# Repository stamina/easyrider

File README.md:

EasyRider
=========

EasyRider is a motorcycle telemetrics project, developed specifically for my Honda C90 classic bike.

The software is written in C for the Atmel AVR ATmega1284p main microcontroller.

The PCB was created with CadSoft Eagle 6.x, you'll find the schematic and board layout (including all components) in the /eagle directory.
The file /doc/info.txt also contains the [BOM] and some project notes. (Partly in Dutch)

_UPDATE:_ EasyRider REV B (github repo: easyriderb) is a completely new, smaller and more advanced board (mostly SMD parts) which also contains a GPS and WiFi module
for easy tracking and communicating with a mobile phone app.

Functionality
-------------

EasyRider basically does the following things:

- Controls the lighting system: indicators, rear light, brake light, etc.
- Controls the claxon
- Contains a simple alarm system, based on an accelerometer
- Reads the motorcycle battery and gives a visual indication of the current voltage
- Contains a little buzzer for some funny startup sounds
- Contains a custom serial UART shell for communication with a terminal program or another microcontroller

Software
--------

The sofware is built around a simple *State Machine* pattern: when the driver is braking or toggling a switch, the software
is sending an event, which is handled by the correct event handler based on the current state (a bitmask of multiple substates).

The buzzer music was created with the **MIDICSV** MIDI to CSV conversion tool. The midi2byte.rb Ruby script converts the
plaintext CSV to a C header file containing an array of music notes.

The custom UART shell code is capable of registering commands and command handlers. E.g. typing "help" or "show state" in TeraTerm, Minicom, Putty
or any other serial terminal program. (configuration: 19200 baud/8N1)

*[BOM]: Bill Of Materials

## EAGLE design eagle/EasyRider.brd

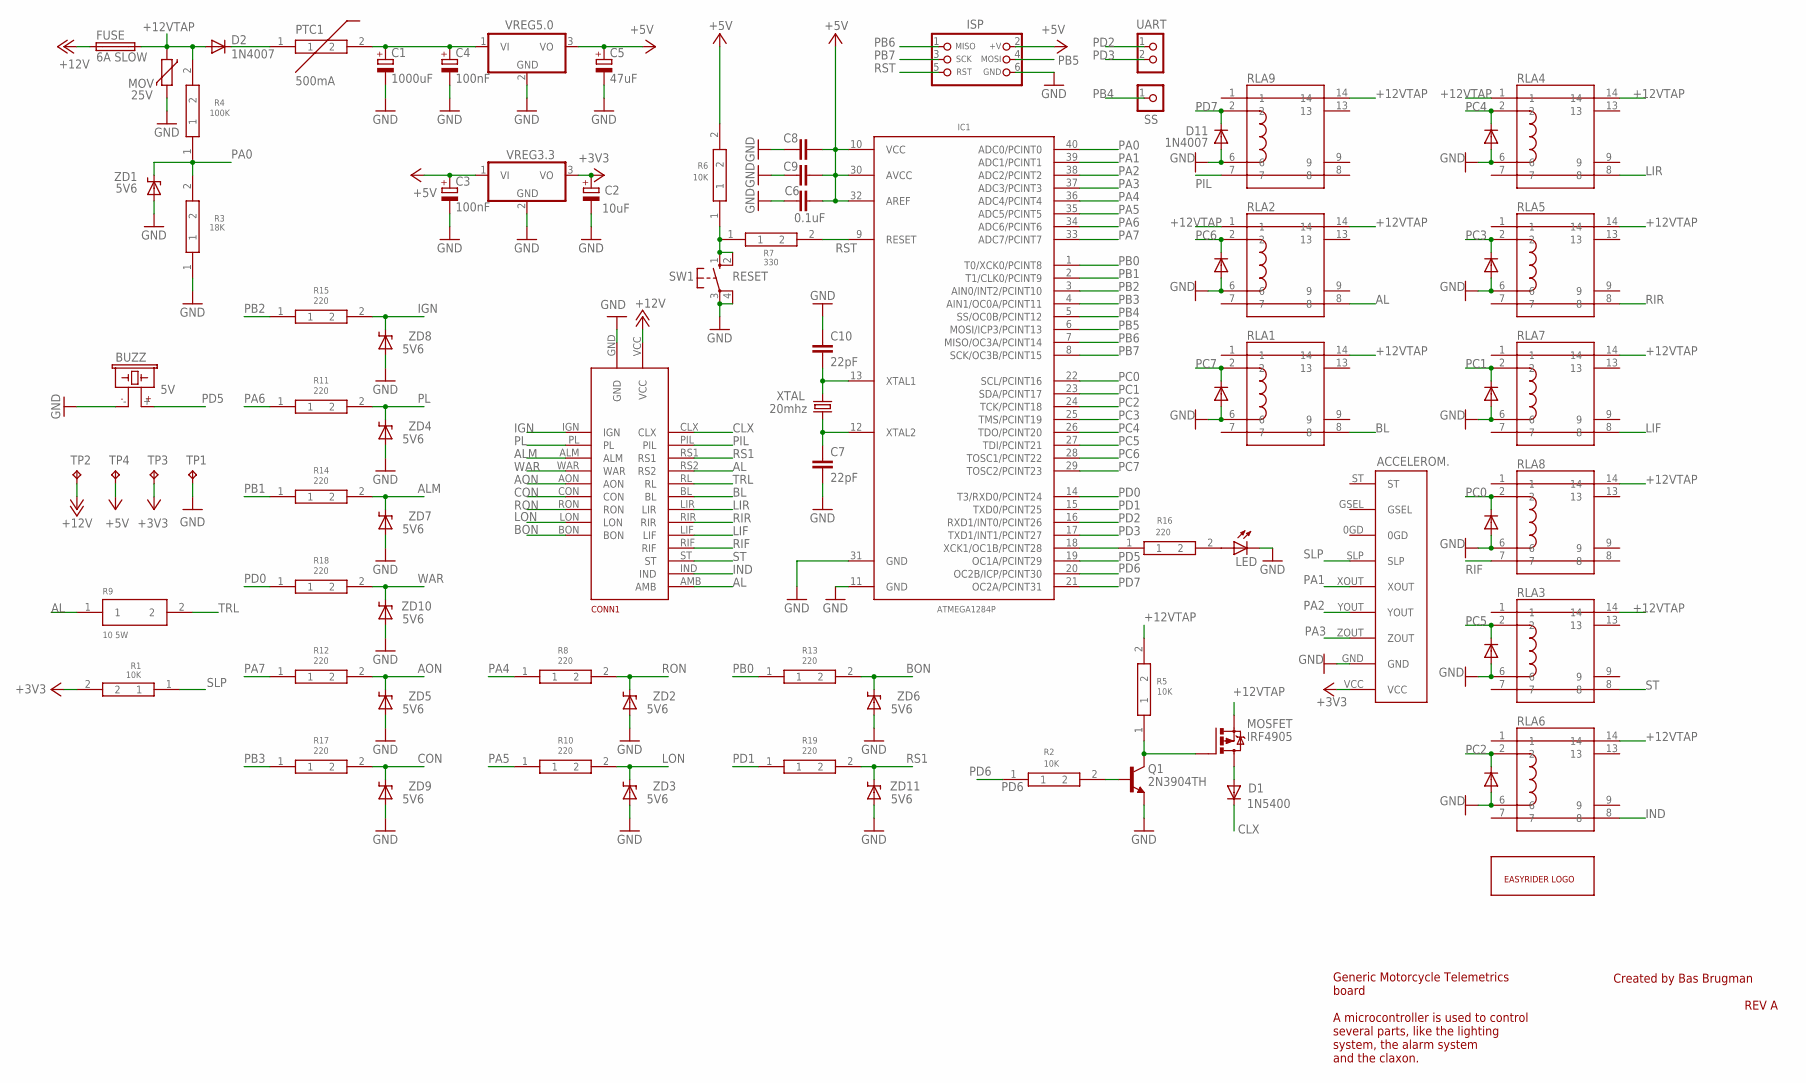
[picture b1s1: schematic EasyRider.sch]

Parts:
ACCELEROM.: MMA7361FREESCALE; BREAKOUT
BUZZ: 5V; 0.3PITCH
C1: 1000uF; E5-10,5
C2: 10uF; E2,5-4R
C3, C4: 100nF; E2,5-4R
C5: 47uF; E2,5-7
C6, C8, C9: 0.1uF; C025-024X044
C7, C10: 22pF; C025-024X044
CONN1: EASYRIDER_CONNDIP; SIL
D1: 1N5400; DO201-15
D2, D11: 1N4007; DIP_1N4007
D3, D4, D5, D6, D7, D8, D9, D10: 1N4007DIP; DIP_1N4007
FUSE: 6A SLOW; SH22,5A
IC1: ATMEGA1284P; DIL40
ISP: CON_HEADER_PRG_AVR_ICSP-PTH; HEADER_PRG_2X03
LED: LEDDIP; LED3MM
MOSFET: IRF4905; TO220
MOV: 25V; R-5
PTC1: 500mA; PTC
Q1: 2N3904TH; TO92
R1, R2, R5, R6: 10K; RESISTOR
R3: 18K; RESISTOR
R4: 100K; RESISTOR
R7: 330; RESISTOR
R8, R10, R11, R12, R13, R14, R15, R16, R17, R18, R19: 220; RESISTOR
R9: 10 5W; RESISTOR
RLA1, RLA2, RLA3, RLA4, RLA5, RLA6, RLA7, RLA8, RLA9: MEDER_REED_DIP05-1A72-12LDIP; DIP05-1A72-12L
SS: CON_HEADER_1X01-PTH; M1X1
SW1: RESET; DIP45MM_56MM_PITCH
TP1, TP2, TP3, TP4: TPTP20SQ; TP20SQ
U$1: EASYRIDER_LOGO
UART: CON_HEADER_1X02-PTH; M1X2
VREG3.3, VREG5.0: VREG_IGODIP; TO220
XTAL: 20mhz; HC49/S
ZD1, ZD2, ZD3, ZD4, ZD5, ZD6, ZD7, ZD8, ZD9, ZD10, ZD11: 5V6; DIODE_ZENER_56

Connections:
+3V3: ACCELEROM..VCC, C2.+, R1.2, TP3.TP, VREG3.3.3 (VO)
+5V: C3.+, C5.+, C6.2, C8.2, C9.2, IC1.10 (VCC), IC1.30 (AVCC), IC1.32 (AREF), ISP.2 (+V), R6.2, TP4.TP, VREG3.3.1 (VI), VREG5.0.3 (VO)
+12V: CONN1.VCC, FUSE.1, TP2.TP
+12VTAP: D2.A, FUSE.2, MOSFET.S, MOV.1, R4.2, R5.2, RLA1.14, RLA2.1, RLA2.14, RLA3.14, RLA4.1, RLA4.14, RLA5.14, RLA6.14, RLA7.14, RLA8.14, RLA9.14
AL: CONN1.AMB, CONN1.RS2, R9.1, RLA2.8
ALM: CONN1.ALM, R14.2, ZD7.C
AON: CONN1.AON, R12.2, ZD5.C
BL: CONN1.BL, RLA1.8
BON: CONN1.BON, R13.2, ZD6.C
CLX: CONN1.CLX, D1.C
CON: CONN1.CON, R17.2, ZD9.C
GND: ACCELEROM..GND, BUZZ.- (1), C1.-, C2.-, C3.-, C4.-, C5.-, C6.1, C7.2, C8.1, C9.1, C10.1, CONN1.GND, D3.A, D4.A, D5.A, D6.A, D7.A, D8.A, D9.A, D10.A, D11.A, IC1.11 (GND), IC1.31 (GND), ISP.6 (GND), LED.K (C), MOV.2, Q1.3 (E), R3.1, RLA1.6, RLA2.6, RLA3.6, RLA4.6, RLA5.6, RLA6.6, RLA7.6, RLA8.6, RLA9.6, SW1.3, SW1.4, TP1.TP, VREG3.3.2 (GND), VREG5.0.2 (GND), ZD1.A, ZD2.A, ZD3.A, ZD4.A, ZD5.A, ZD6.A, ZD7.A, ZD8.A, ZD9.A, ZD10.A, ZD11.A
IGN: CONN1.IGN, R15.2, ZD8.C
IND: CONN1.IND, RLA6.8
LIF: CONN1.LIF, RLA7.8
LIR: CONN1.LIR, RLA4.8
LON: CONN1.LON, R10.2, ZD3.C
unnamed: C7.1, IC1.12 (XTAL2), XTAL.1
unnamed: C10.2, IC1.13 (XTAL1), XTAL.2
unnamed: R6.1, R7.1, SW1.1, SW1.2
unnamed: IC1.18 (XCK1/OC1B/PCINT28), R16.1
unnamed: MOSFET.G, Q1.1 (C), R5.1
unnamed: D1.A, MOSFET.D
unnamed: LED.A, R16.2
unnamed: C1.+, C4.+, PTC1.2, VREG5.0.1 (VI)
unnamed: D2.C, PTC1.1
unnamed: Q1.2 (B), R2.2
PA0: IC1.40 (ADC0/PCINT0), R3.2, R4.1, ZD1.C
PA1: ACCELEROM..XOUT, IC1.39 (ADC1/PCINT1)
PA2: ACCELEROM..YOUT, IC1.38 (ADC2/PCINT2)
PA3: ACCELEROM..ZOUT, IC1.37 (ADC3/PCINT3)
PA4: IC1.36 (ADC4/PCINT4), R8.1
PA5: IC1.35 (ADC5/PCINT5), R10.1
PA6: IC1.34 (ADC6/PCINT6), R11.1
PA7: IC1.33 (ADC7/PCINT7), R12.1
PB0: IC1.1 (T0/XCK0/PCINT8), R13.1
PB1: IC1.2 (T1/CLK0/PCINT9), R14.1
PB2: IC1.3 (AIN0/INT2/PCINT10), R15.1
PB3: IC1.4 (AIN1/OC0A/PCINT11), R17.1
PB4: IC1.5 (SS/OC0B/PCINT12), SS.1
PB5: IC1.6 (MOSI/ICP3/PCINT13), ISP.4 (MOSI)
PB6: IC1.7 (MISO/OC3A/PCINT14), ISP.1 (MISO)
PB7: IC1.8 (SCK/OC3B/PCINT15), ISP.3 (SCK)
PC0: D10.C, IC1.22 (SCL/PCINT16), RLA8.2
PC1: D9.C, IC1.23 (SDA/PCINT17), RLA7.2
PC2: D8.C, IC1.24 (TCK/PCINT18), RLA6.2
PC3: D7.C, IC1.25 (TMS/PCINT19), RLA5.2
PC4: D6.C, IC1.26 (TDO/PCINT20), RLA4.2
PC5: D5.C, IC1.27 (TDI/PCINT21), RLA3.2
PC6: D4.C, IC1.28 (TOSC1/PCINT22), RLA2.2
PC7: D3.C, IC1.29 (TOSC2/PCINT23), RLA1.2
PD0: IC1.14 (T3/RXD0/PCINT24), R18.1
PD1: IC1.15 (TXD0/PCINT25), R19.1
PD2: IC1.16 (RXD1/INT0/PCINT26), UART.1
PD3: IC1.17 (TXD1/INT1/PCINT27), UART.2
PD5: BUZZ.+ (2), IC1.19 (OC1A/PCINT29)
PD6: IC1.20 (OC2B/ICP/PCINT30), R2.1
PD7: D11.C, IC1.21 (OC2A/PCINT31), RLA9.2
PIL: CONN1.PIL, RLA9.7
PL: CONN1.PL, R11.2, ZD4.C
RIF: CONN1.RIF, RLA8.7
RIR: CONN1.RIR, RLA5.8
RON: CONN1.RON, R8.2, ZD2.C
RS1: CONN1.RS1, R19.2, ZD11.C
RST: IC1.9 (RESET), ISP.5 (RST), R7.2
SLP: ACCELEROM..SLP, R1.1
ST: CONN1.ST, RLA3.8
TRL: CONN1.RL, R9.2
WAR: CONN1.WAR, R18.2, ZD10.C

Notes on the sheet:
Created by Bas Brugman
REV A
Generic Motorcycle Telemetrics board A microcontroller is used to control several parts, like the lighting system, the alarm system and the claxon.

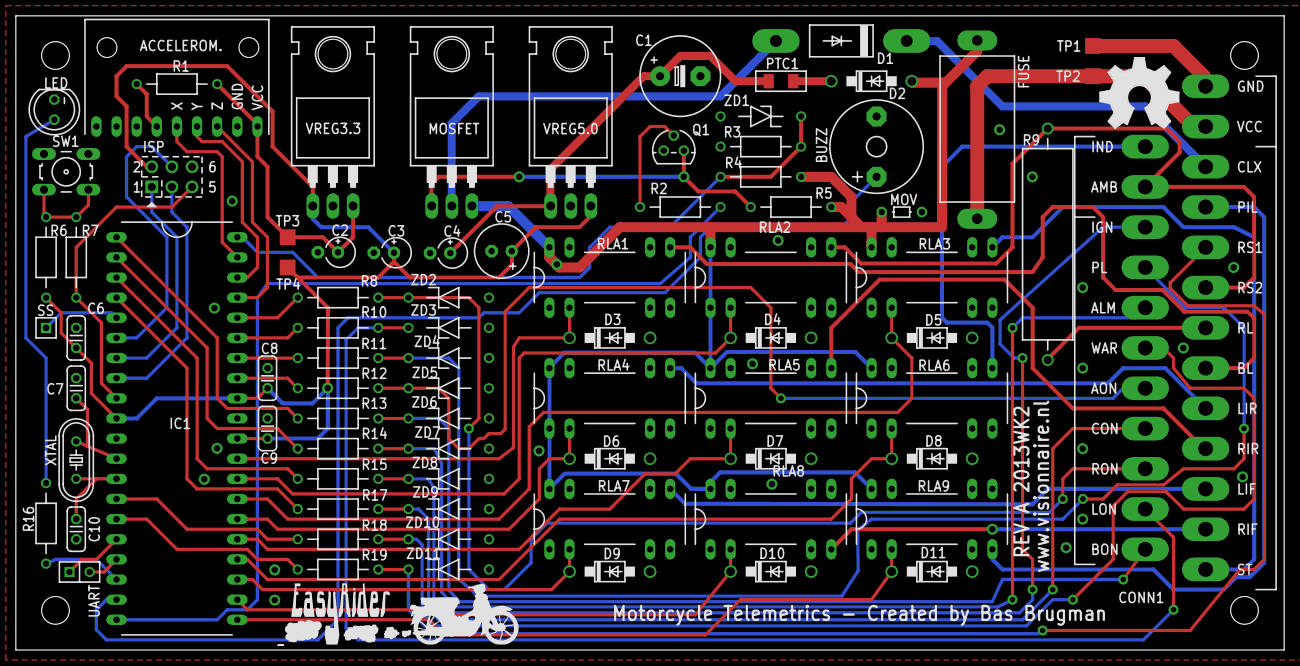
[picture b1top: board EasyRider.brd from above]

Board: 2 copper layers, 160.0 x 80.0 mm, 83 parts (0 on the bottom side), 69 nets.

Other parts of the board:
U$2: OSHW_FILLX350_NOTEXT

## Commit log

2013-03-11 Added readme
2013-03-12 Expanding readme
2013-03-24 Change alarm trigger time and fixed buzzer sound when turning ignition off
2013-03-24 Alarm indicator speed issue
2013-03-24 Minor alarm mode changes
2013-03-29 Fixed a bug which caused the claxon sound to continue, even when the alarm was turned off
2013-06-24 Todo changes
2013-08-31 Starting REV B
2013-09-13 Preparing for REV B
2013-10-09 Todo changes for REV B
2013-10-26 More info for REV B
2013-10-30 Extracted REV B Board and Software to its own repository, REV A will contain only bug fixes from now on
2013-10-30 README changes
2013-11-01 Adding pinout diagram as a quick reminder
